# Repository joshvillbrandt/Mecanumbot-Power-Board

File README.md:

Mecanumbot Power Board
======================

The power board for the Mecanumbot robot.

## Features

* automatically selects between two batteries and the wall
* chooses the wall if available, otherwise drains the batteries one at a time
* provides power voltage and current measuring
* communicates to the primary vehicle Arduino over I2C
* provides regulated 5V power for the robot LEDs
* provides pins for an external switch

See more at http://javconcepts.com/2013/01/06/mecanumbot-power-board/.

## Todo List

* add battery charging
 * the [MAX164*](http://www.maximintegrated.com/datasheet/index.mvp/id/1751) can [allegedly](http://letsmakerobots.com/node/28374?page=1) charge up to a six cell lipo; i'm not sure if that includes balancing the cell or not too
* add fusing
* keep the board / robot powered during microcontroller restart by using flip-flops (useful for loading new code from the robot itself)
 * this could enable comm directly with ROS via USB instead of through I2C through the other Arduino!

## Screenshot

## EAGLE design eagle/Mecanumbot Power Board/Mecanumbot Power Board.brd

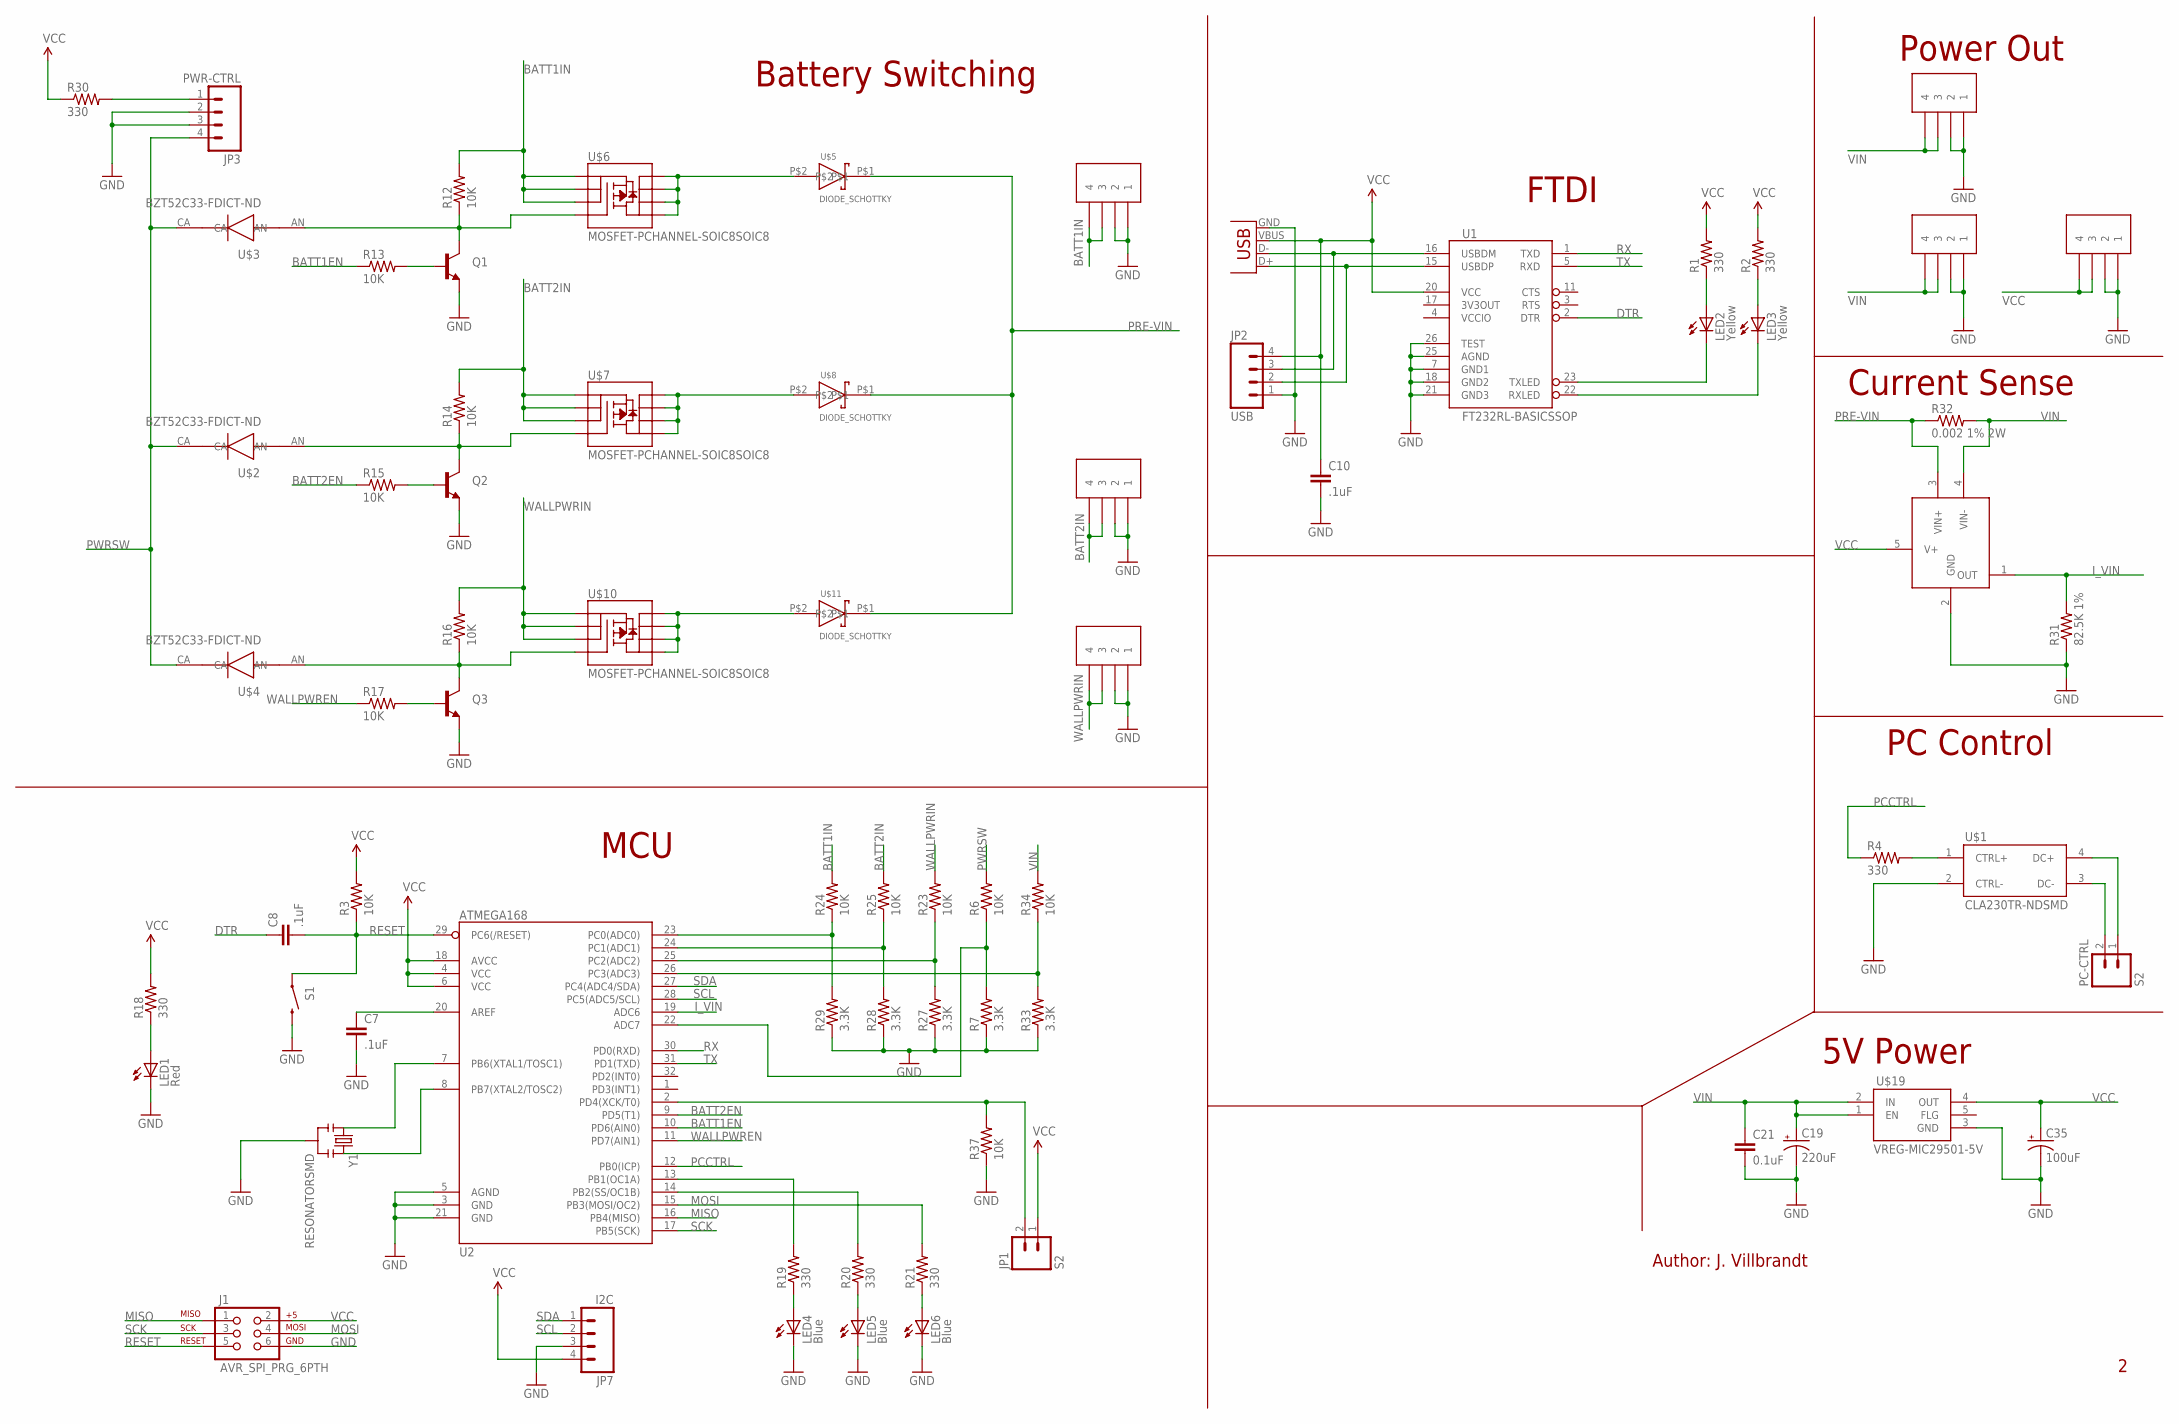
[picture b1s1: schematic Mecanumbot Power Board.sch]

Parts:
C7, C8, C10: .1uF; 0603-CAP
C19: 220uF; CPOL-RADIAL-1000UF-25V
C21: 0.1uF; 1206
C35: 100uF; EIA3216
J1: AVR_SPI_PRG_6PTH; 2X3
JP1: S2; 1X02
JP2: USB; 1X04
JP3: PWR-CTRL; 1X04
JP7: I2C; 1X04
LED1: Red; LED-0603
LED2, LED3: Yellow; LED-0603
LED4, LED5, LED6: Blue; LED-0603
PC-CTRL: S2; 1X02
Q1, Q2, Q3: TRANSISTOR_NPNSOT23; SOT23
R1, R2, R4, R18, R19, R20, R21, R30: 330; 0603-RES
R3, R6, R12, R13, R14, R15, R16, R17, R23, R24, R25, R34, R37: 10K; 0603-RES
R7, R27, R28, R29, R33: 3.3K; 0603-RES
R31: 82.5K 1%; 0603-RES
R32: 0.002 1% 2W; R2512
S1: reset; TACTILE_SWITCH_SMD
U1: FT232RL-BASICSSOP; SSOP28DB
U2: ATMEGA168; TQFP32-08
U$1: CLA230TR-NDSMD; 4-SOP
U$2, U$3, U$4: BZT52C33-FDICT-ND; SOD-123
U$5, U$8, U$11: DIODE_SCHOTTKY; DO214AB
U$6, U$7, U$10: MOSFET-PCHANNEL-SOIC8SOIC8; SO08
U$12, U$13, U$14, U$16, U$17, U$18: TERMINAL-4MINIFIT-JR; MINIFITJR-RGT-4
U$19: VREG-MIC29501-5V; TO263-5
U$20: INA139/169SOT23-5; SOT23-5
X1: USBSMD; USB-MINIB
Y1: RESONATORSMD; RESONATOR-SMD

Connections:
BATT1EN: R13.1, U2.10 (PD6(AIN0))
BATT1IN: R12.2, R24.2, U$6.1 (S), U$6.2 (S), U$6.3 (S), U$12.3, U$12.4
BATT1PREDIODE: U$5.P$2, U$6.5 (D), U$6.6 (D), U$6.7 (D), U$6.8 (D)
BATT2EN: R15.1, U2.9 (PD5(T1))
BATT2IN: R14.2, R25.2, U$7.1 (S), U$7.2 (S), U$7.3 (S), U$13.3, U$13.4
BATT2PREDIODE: U$7.5 (D), U$7.6 (D), U$7.7 (D), U$7.8 (D), U$8.P$2
DTR: C8.1, U1.2 (DTR)
GND: C7.2, C10.2, C19.2 (-), C21.2, C35.C (-), J1.6, JP2.1, JP3.2, JP3.3, JP7.3, LED1.C, LED4.C, LED5.C, LED6.C, Q1.2 (E), Q2.2 (E), Q3.2 (E), R7.1, R27.1, R28.1, R29.1, R31.1, R33.1, R37.1, S1.3 (2), U1.7 (GND1), U1.18 (GND2), U1.21 (GND3), U1.25 (AGND), U1.26 (TEST), U2.3 (GND), U2.5 (AGND), U2.21 (GND), U$1.2 (CTRL-), U$12.1, U$12.2, U$13.1, U$13.2, U$14.1, U$14.2, U$16.1, U$16.2, U$17.1, U$17.2, U$18.1, U$18.2, U$19.3 (GND), U$20.2 (GND), X1.GND, Y1.2
I_VIN: R31.2, U2.19 (ADC6), U$20.1 (OUT)
MISO: J1.1, U2.16 (PB4(MISO))
MOSI: J1.4, R21.2, U2.15 (PB3(MOSI/OC2))
unnamed: LED2.A, R1.1
unnamed: LED3.A, R2.1
unnamed: LED2.C, U1.23 (TXLED)
unnamed: LED3.C, U1.22 (RXLED)
unnamed: PC-CTRL.2, U$1.3 (DC-)
unnamed: PC-CTRL.1, U$1.4 (DC+)
unnamed: JP2.3, U1.16 (USBDM), X1.D-
unnamed: JP2.2, U1.15 (USBDP), X1.D+
unnamed: C7.1, U2.20 (AREF)
unnamed: U2.7 (PB6(XTAL1/TOSC1)), Y1.1
unnamed: U2.8 (PB7(XTAL2/TOSC2)), Y1.3
unnamed: R4.2, U$1.1 (CTRL+)
unnamed: JP3.1, R30.2
unnamed: R20.2, U2.14 (PB2(SS/OC1B))
unnamed: R33.2, R34.1, U2.26 (PC3(ADC3))
unnamed: R19.2, U2.13 (PB1(OC1A))
unnamed: JP1.2, R37.2, U2.2 (PD4(XCK/T0))
unnamed: Q1.3 (C), R12.1, U$3.AN, U$6.4 (G)
unnamed: Q1.1 (B), R13.2
unnamed: Q2.3 (C), R14.1, U$2.AN, U$7.4 (G)
unnamed: Q2.1 (B), R15.2
unnamed: LED1.A, R18.1
unnamed: Q3.3 (C), R16.1, U$4.AN, U$10.4 (G)
unnamed: Q3.1 (B), R17.2
unnamed: LED6.A, R21.1
unnamed: LED4.A, R19.1
unnamed: LED5.A, R20.1
unnamed: R23.1, R27.2, U2.25 (PC2(ADC2))
unnamed: R25.1, R28.2, U2.24 (PC1(ADC1))
unnamed: R24.1, R29.2, U2.23 (PC0(ADC0))
unnamed: R6.1, R7.2, U2.22 (ADC7)
PCCTRL: R4.1, U2.12 (PB0(ICP))
PRE-VIN: R32.1, U$5.P$1, U$8.P$1, U$11.P$1, U$20.3 (VIN+)
PWRSW: JP3.4, R6.2, U$2.CA, U$3.CA, U$4.CA
RESET: C8.2, J1.5, R3.1, S1.1, U2.29 (PC6(/RESET))
RX: U1.1 (TXD), U2.30 (PD0(RXD))
SCK: J1.3, U2.17 (PB5(SCK))
SCL: JP7.2, U2.28 (PC5(ADC5/SCL))
SDA: JP7.1, U2.27 (PC4(ADC4/SDA))
TX: U1.5 (RXD), U2.31 (PD1(TXD))
VCC: C10.1, C35.A (+), J1.2, JP1.1, JP2.4, JP7.4, R1.2, R2.2, R3.2, R18.2, R30.1, U1.20 (VCC), U2.4 (VCC), U2.6 (VCC), U2.18 (AVCC), U$18.3, U$18.4, U$19.4 (OUT), U$20.5 (V+), X1.VBUS
VCCIO: U1.4 (VCCIO)
VIN: C19.1 (+), C21.1, R32.2, R34.2, U$16.3, U$16.4, U$17.3, U$17.4, U$19.1 (EN), U$19.2 (IN), U$20.4 (VIN-)
WALLPWREN: R17.1, U2.11 (PD7(AIN1))
WALLPWRIN: R16.2, R23.2, U$10.1 (S), U$10.2 (S), U$10.3 (S), U$14.3, U$14.4
WALLPWRPREDIODE: U$10.5 (D), U$10.6 (D), U$10.7 (D), U$10.8 (D), U$11.P$2

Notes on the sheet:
Battery Switching
MCU
FTDI
5V Power
Power Out
Current Sense
Author: J. Villbrandt
PC Control

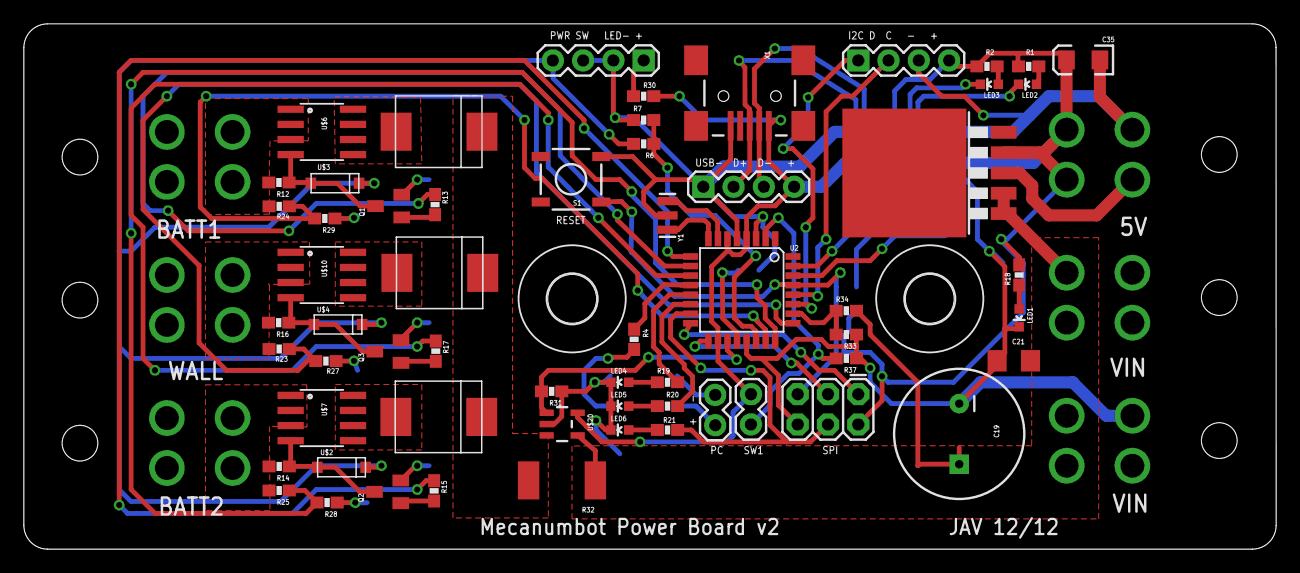
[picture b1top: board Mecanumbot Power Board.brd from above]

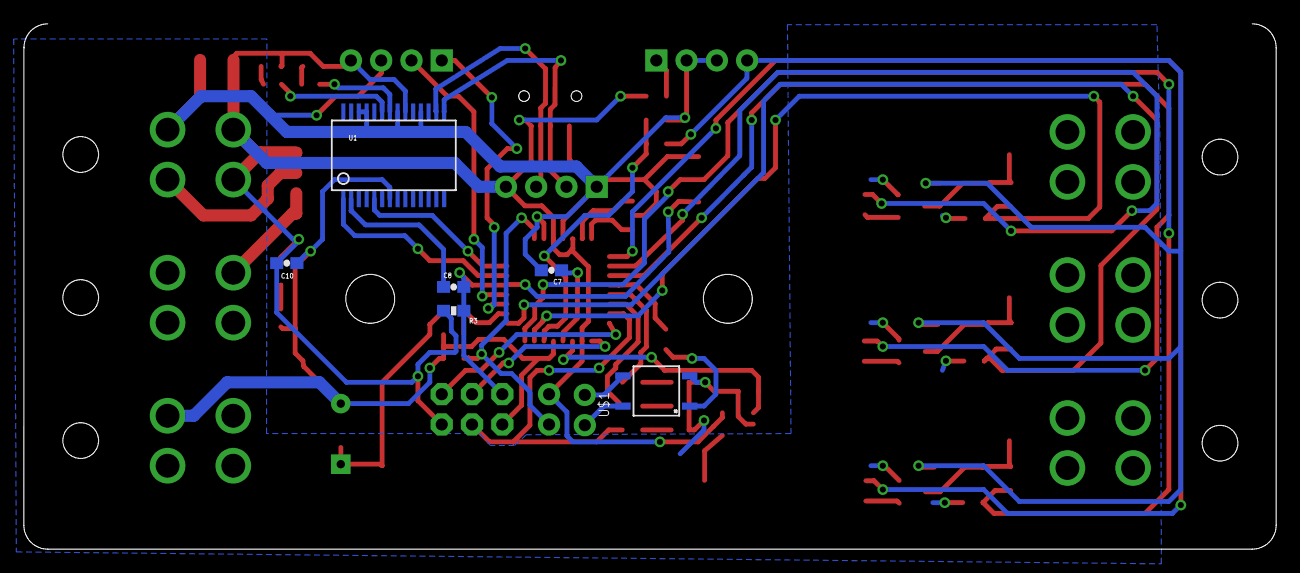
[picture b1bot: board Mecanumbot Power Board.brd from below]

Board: 2 copper layers, 105.1 x 44.1 mm, 74 parts (6 on the bottom side), 56 nets.

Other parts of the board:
U$24, U$26: 4,1

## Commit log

2013-12-19 initial commit from svn
2013-12-19 old version of the .brd file
2013-12-24 pushing rev 1.0 from svn
2013-12-24 pushing back version 1.0 from svn
2013-12-24 pushing back v2.0 from svn
2013-12-24 updated title
2014-01-07 added battery charging circuit links
